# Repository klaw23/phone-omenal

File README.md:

# Phone-omenal 📞

**An open source telephone.** A box with an analog phone jack: plug in any
phone — a 1962 rotary, a Mickey Mouse phone, whatever the thrift store had —
and it calls other phones on your network through an open switchboard server
you (or anyone) can run. Everything is open: enclosure, electronics, firmware,
server.

The commercial inspiration is the Tin Can kids' landline; this is the
non-commercial, hackable, federated cousin.

## The build: ESP32 + a SLIC module + any old phone

**Start with [docs/esp32-build-guide.md](docs/esp32-build-guide.md).** It's the
whole project: complete parts and tools shopping list (~$120 all-in, no
soldering), a hardware crash course written for software engineers, and six
milestones — each one ends with something you can see or hear:

1. **Milestone 0** — stand up the Asterisk switchboard in Docker, call between
   two softphones (do this before any parts arrive)
2. **Hello world** — ESP-IDF toolchain, first flash
3. **Hook detection** — lift the handset, watch the serial log react
4. **Ring** — a real bell hammers because your for-loop said so
5. **Dial tone** — 350Hz + 440Hz through a real earpiece
6. **Digits** — decode rotary pulses (and touch-tones)
7. **The call** — dial 600 on a rotary phone, hear yourself echo back via SIP

## Repo layout

| Path | What |
|---|---|
| `docs/` | **The build guide — start here** · plus the provisioning & switchboard spec |
| `server/` | Asterisk switchboard + management web app: `docker compose up -d` and go |
| `firmware/` | Milestone example code matching the guide |
| `hardware/enclosure/` | Model 01 printed enclosure (OpenSCAD + STLs + 3D viewer) — fits the guide's electronics once they graduate from breadboard to perfboard |
| `future/` | Future work, tucked away: the Model 02 custom PCB and its smaller enclosure. Ignore until the breadboard build is making calls |

## Licenses

- Firmware & server configs: **MIT**
- Hardware (enclosure, PCB): **CERN-OHL-S v2**
- Documentation: **CC BY-SA 4.0**

## Standing on shoulders

[RetroPhone](https://github.com/ktownsend-personal/RetroPhone) proved the
ESP32+SLIC phone interface; [ESP32-SIP-Voice](https://github.com/GeorgeBregman/ESP32-SIP-Voice)
provides the SIP stack; [Asterisk](https://www.asterisk.org/) is the switch;
[PhreakNet](https://phreaknet.org/) and [NPSTN](https://npstn.us) showed hobbyist
phone networks are a thriving genre.

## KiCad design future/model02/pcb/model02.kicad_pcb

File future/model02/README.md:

# Future work: Model 02 — the custom PCB

**Not the current project.** The current project is the ESP32 breadboard build
in `docs/esp32-build-guide.md`. This directory is a head start on what comes
*after* that works: collapsing the Audio Kit + perfboard + modules into a single
custom 80×54mm board, in a box half the size.

What's here, for when that day comes:

- `pcb/model02.kicad_pcb` — routed KiCad board (machine-routed rev A,
  DRC-clean electrically, **not yet reviewed by human eyes** — read
  `pcb/model02_board_design.md` §8 before spending money)
- `pcb/gerbers/` + `pcb/model02_bom.csv` + `pcb/model02_cpl_top.csv` — the
  JLCPCB upload set
- `pcb/model02_board_design.md` — the full engineering design doc
- `pcb/generator/` — the Python scripts that generate and route the board
- `model02.scad` / STLs / viewer — the matching smaller enclosure (91×65×28mm)

The right time to open this folder: the breadboard build makes calls reliably,
the firmware has settled, and you want ten of these instead of one.

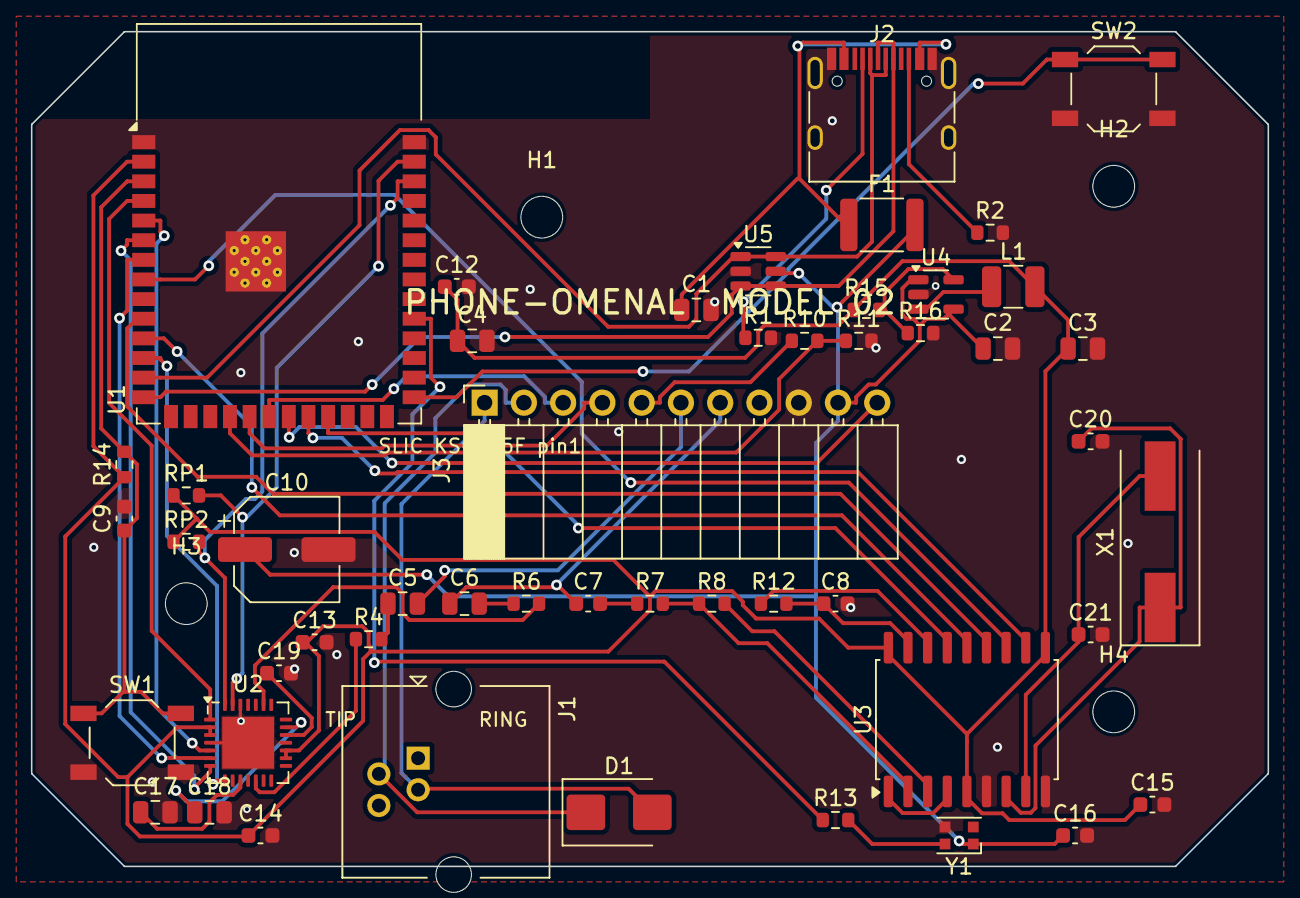
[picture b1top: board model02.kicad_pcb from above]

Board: 2 copper layers, 80.0 x 54.0 mm, 54 parts (0 on the bottom side), 50 nets.

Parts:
C1, C2, C3, C4: 22uF; C_0805_2012Metric
C5, C6: 4.7uF; C_0805_2012Metric
C7, C8, C12, C13, C14, C15, C16, C19: 100nF; C_0603_1608Metric
C9: 1uF; C_0603_1608Metric
C10: 100uF; CP_Elec_6.3x5.8
C17, C18: 10uF; C_0805_2012Metric
C20, C21: 18pF; C_0603_1608Metric
D1: SMBJ100CA; D_SMB
F1: 1A polyfuse; Fuse_1812_4532Metric
H1, H2, H3, H4: MountingHole_2.7mm_M2.5
J1: RJ11-6P4C; RJ14_Connfly_DS1133-S4_Horizontal
J2: USB-C 16pin; USB_C_Receptacle_HRO_TYPE-C-31-M-12
J3: KS0835F socket; PinSocket_1x11_P2.54mm_Horizontal
L1: 2.2uH; L_1210_3225Metric
R1, R2: 5.1k; R_0603_1608Metric
R4: 100R; R_0603_1608Metric
R6, R10, R14: 10k; R_0603_1608Metric
R7, R8, R15: 100k; R_0603_1608Metric
R11: 15k; R_0603_1608Metric
R12: 300k; R_0603_1608Metric
R13: 330R; R_0603_1608Metric
R16: 22k; R_0603_1608Metric
RP1, RP2: 4.7k; R_0603_1608Metric
SW1: EN; SW_SPST_TL3342
SW2: BOOT; SW_SPST_TL3342
U1: ESP32-S3-WROOM-1-N8R2; ESP32-S3-WROOM-1
U2: ES8388; QFN-28-1EP_5x5mm_P0.5mm_EP3.35x3.35mm
U3: HT9170D; SOIC-18W_7.5x11.6mm_P1.27mm
U4: SY8089AAAC; SOT-23-5
U5: USBLC6-2SC6; SOT-23-6
X1: 3.579545MHz; Crystal_SMD_HC49-SD
Y1: WS2812B-2020; LED_WS2812B-2020_PLCC4_2.0x2.0mm

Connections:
+3V3: C3.1, C4.1, C12.1, C13.1, C14.1, C15.1, L1.2, R14.1, R15.1, RP1.1, RP2.1, U1.2, U2.2, U2.3, U2.16, U2.17, U3.5, U3.10, U3.18
+5V: C2.1, C10.1, C16.1, F1.2, J3.10, U4.1, U4.4, U5.5, Y1.1
AUD_LOUT1: R4.1, U2.12
AUD_LOUT_C: C5.1, R4.2
AUD_RIN1: R6.2, U2.23
BOOT: SW2.1, U1.27
BUCK_FB: R15.2, R16.1, U4.5
BUCK_LX: L1.1, U4.3
CC1: J2.A5, R1.1
CC2: J2.B5, R2.1
DTMF_C: C7.2, R7.1
DTMF_DV: U1.23, U3.15
DTMF_EST: R12.1, U3.16
DTMF_GS: R8.2, U3.3
DTMF_IN: R7.2, R8.1, U3.2
DTMF_Q1: U1.22, U3.11
DTMF_Q2: U1.8, U3.12
DTMF_Q3: U1.10, U3.13
DTMF_Q4: U1.11, U3.14
DTMF_STGT: C8.1, R12.2, U3.17
DTMF_VREF: U3.1, U3.4
EN: C9.1, R14.2, SW1.1, U1.3
ES_ADCVREF: C19.1, U2.19
ES_VMID: C18.1, U2.20
ES_VREF: C17.1, U2.10
GND: C1.2, C2.2, C3.2, C4.2, C8.2, C9.2, C10.2, C12.2, C13.2, C14.2, C15.2, C16.2, C17.2, C18.2, C19.2, C20.2, C21.2, J2.A1, J2.A12, J2.B1, J2.B12, J2.S1, J3.9, R1.2, R2.2, R11.2, R16.2, SW1.2, SW2.2, U1.1, U1.40, U1.41, U2.4, U2.18, U2.26, U2.29, U3.6, U3.9, U4.2, U5.2, Y1.3
I2C_SCL: RP2.2, U1.38, U2.28
I2C_SDA: RP1.2, U1.39, U2.27
I2S_BCLK: U1.5, U2.5
I2S_DIN: U1.12, U2.8
I2S_DOUT: U1.7, U2.6
I2S_LRCK: U1.6, U2.7
I2S_MCLK: U1.4, U2.1
LED_DATA: R13.2, Y1.4
LED_R: R13.1, U1.31
OSC1: C20.1, U3.7, X1.1
OSC2: C21.1, U3.8, X1.2
RING: D1.2, J1.3, J3.1
SLIC_FR: J3.3, U1.20
SLIC_PD: J3.11, U1.21
SLIC_RM: J3.4, U1.19
SLIC_SHK: R10.2, R11.1, U1.18
SLIC_SHK_5V: J3.5, R10.1
TIP: D1.1, J1.2, J3.2
USB_DM: J2.A7, J2.B7, U1.13, U5.1, U5.6
USB_DP: J2.A6, J2.B6, U1.14, U5.3, U5.4
VBUS_RAW: C1.1, F1.1, J2.A4, J2.A9, J2.B4, J2.B9
VR_IN: C5.2, J3.6
VX_C: C6.2, R6.1
VX_OUT: C6.1, C7.1, J3.7

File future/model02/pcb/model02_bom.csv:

Designator,Value,Footprint,MPN / note
U1,ESP32-S3-WROOM-1-N8R2,ESP32-S3-WROOM-1,ESP32-S3-WROOM-1-N8R2
U2,ES8388,QFN-28-1EP_5x5mm_P0.5mm_EP3.35x3.35mm,ES8388
U3,HT9170D,SOIC-18W_7.5x11.6mm_P1.27mm,HT9170D
U4,SY8089AAAC,SOT-23-5,SY8089AAAC
U5,USBLC6-2SC6,SOT-23-6,USBLC6-2SC6
J1,RJ11-6P4C,RJ14_Connfly_DS1133-S4_Horizontal,RJ11 6P4C DS1133-S4
J2,USB-C 16pin,USB_C_Receptacle_HRO_TYPE-C-31-M-12,TYPE-C-31-M-12
J3,KS0835F socket,PinSocket_1x11_P2.54mm_Horizontal,2.54mm 1x11 R/A socket
F1,1A polyfuse,Fuse_1812_4532Metric,MF-MSMF100
D1,SMBJ100CA,D_SMB,SMBJ100CA
L1,2.2uH,L_1210_3225Metric,generic 2.2uH
X1,3.579545MHz,Crystal_SMD_HC49-SD,3.579545MHz HC49-SMD
Y1,WS2812B-2020,LED_WS2812B-2020_PLCC4_2.0x2.0mm,WS2812B-2020
SW1,EN,SW_SPST_TL3342,generic EN
SW2,BOOT,SW_SPST_TL3342,generic BOOT
R1,5.1k,R_0603_1608Metric,generic 5.1k
R2,5.1k,R_0603_1608Metric,generic 5.1k
R4,100R,R_0603_1608Metric,generic 100R
R6,10k,R_0603_1608Metric,generic 10k
R7,100k,R_0603_1608Metric,generic 100k
R8,100k,R_0603_1608Metric,generic 100k
R10,10k,R_0603_1608Metric,generic 10k
R11,15k,R_0603_1608Metric,generic 15k
R12,300k,R_0603_1608Metric,generic 300k
R13,330R,R_0603_1608Metric,generic 330R
R14,10k,R_0603_1608Metric,generic 10k
R15,100k,R_0603_1608Metric,generic 100k
R16,22k,R_0603_1608Metric,generic 22k
RP1,4.7k,R_0603_1608Metric,generic 4.7k
RP2,4.7k,R_0603_1608Metric,generic 4.7k
C1,22uF,C_0805_2012Metric,generic 22uF
C2,22uF,C_0805_2012Metric,generic 22uF
C3,22uF,C_0805_2012Metric,generic 22uF
C4,22uF,C_0805_2012Metric,generic 22uF
C5,4.7uF,C_0805_2012Metric,generic 4.7uF
C6,4.7uF,C_0805_2012Metric,generic 4.7uF
C7,100nF,C_0603_1608Metric,generic 100nF
C8,100nF,C_0603_1608Metric,generic 100nF
C9,1uF,C_0603_1608Metric,generic 1uF
C10,100uF,CP_Elec_6.3x5.8,generic 100uF
C12,100nF,C_0603_1608Metric,generic 100nF
C13,100nF,C_0603_1608Metric,generic 100nF
C14,100nF,C_0603_1608Metric,generic 100nF
C15,100nF,C_0603_1608Metric,generic 100nF
C16,100nF,C_0603_1608Metric,generic 100nF
C17,10uF,C_0805_2012Metric,generic 10uF
C18,10uF,C_0805_2012Metric,generic 10uF
C19,100nF,C_0603_1608Metric,generic 100nF
C20,18pF,C_0603_1608Metric,generic 18pF
C21,18pF,C_0603_1608Metric,generic 18pF

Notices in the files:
future/model02/pcb/model02.kicad_pcb:
open source telephone - CERN-OHL-S
